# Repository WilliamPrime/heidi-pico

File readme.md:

HeidiBoard is my first attempt at a designing a devboard

Here are some features
- rp2040 microprocessor
- 16MiB of flash
- 1 wire temperature sensor
- pin compatible with pi pico
- fun Heidi artwork

here are some photos from design it:

here are some photos of the assembled working boards:
(to be added later)

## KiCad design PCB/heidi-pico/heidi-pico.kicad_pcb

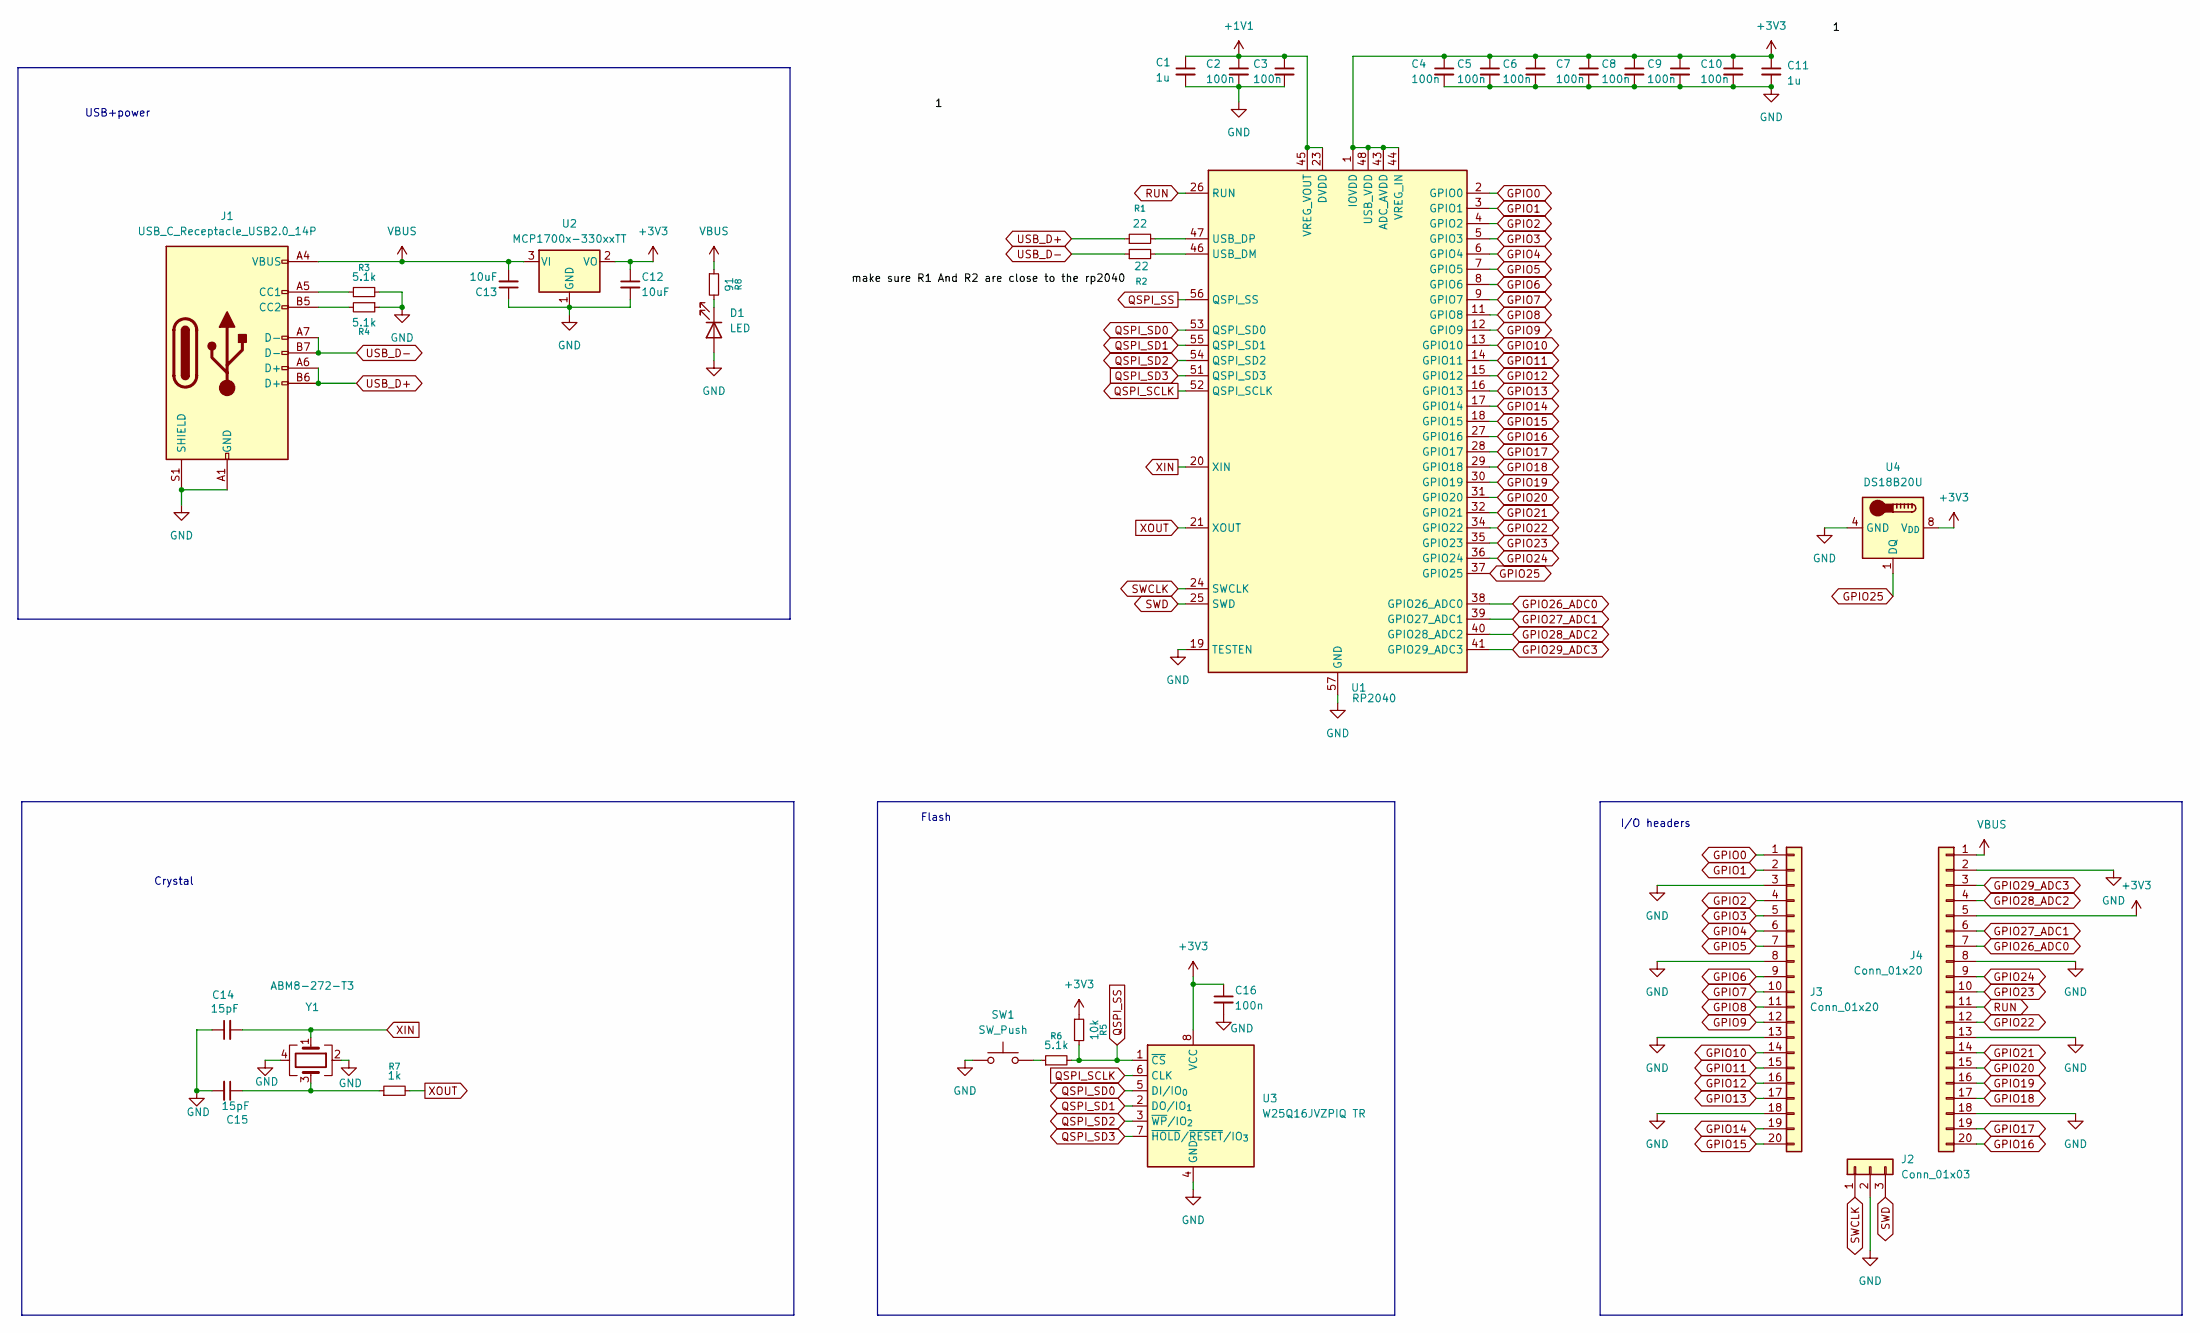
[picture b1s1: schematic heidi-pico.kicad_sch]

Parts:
C1, C11: 1u; C_0402_1005Metric
C2, C3, C4, C5, C6, C7, C8, C9, C10, C16: 100n; C_0402_1005Metric
C12, C13: 10uF; C_0603_1608Metric
C14, C15: 15pF; C_0402_1005Metric
D1: LED; LED_0603_1608Metric
J1: USB_C_Receptacle_USB2.0_14P; USB_C_Receptacle_HRO_TYPE-C-31-M-12
J2: Conn_01x03; PinHeader_1x03_P2.54mm_Vertical
J3, J4: Conn_01x20; PinHeader_1x20_P2.54mm_Vertical
R1, R2: 22; R_0402_1005Metric
R3, R4, R6: 5.1k; R_0402_1005Metric
R5: 10k; R_0402_1005Metric
R7: 1k; R_0402_1005Metric
R8: 91; R_0603_1608Metric
SW1: SW_Push; pushSwitch
U1: RP2040; QFN-56-1EP_7x7mm_P0.4mm_EP3.2x3.2mm
U2: MCP1700x-330xxTT; SOT-23
U3: W25Q16JVZPIQ TR; Winbond_USON-8-1EP_3x2mm_P0.5mm_EP0.2x1.6mm
U4: DS18B20U; MSOP-8_3x3mm_P0.65mm
Y1: ABM8-272-T3; Crystal_SMD_Abracon_ABM8G-4Pin_3.2x2.5mm

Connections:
+1V1: C1.1, C2.1, C3.1, U1.23 (DVDD), U1.45 (VREG_VOUT), U1.50 (DVDD)
+3V3: C4.1, C5.1, C6.1, C7.1, C8.1, C9.1, C10.1, C11.1, C12.1, C16.1, J4.5, R5.1, U1.1 (IOVDD), U1.10 (IOVDD), U1.22 (IOVDD), U1.33 (IOVDD), U1.42 (IOVDD), U1.43 (ADC_AVDD), U1.44 (VREG_IN), U1.48 (USB_VDD), U1.49 (IOVDD), U2.2 (VO), U3.8 (VCC), U4.8 (V_{DD})
GND: C1.2, C2.2, C3.2, C4.2, C5.2, C6.2, C7.2, C8.2, C9.2, C10.2, C11.2, C12.2, C13.1, C14.1, C15.2, C16.2, D1.2 (A), J1.A1 (GND), J1.A12 (GND), J1.B1 (GND), J1.B12 (GND), J1.S1 (SHIELD), J2.2, J3.3, J3.8, J3.13, J3.18, J4.2, J4.8, J4.13, J4.18, R3.2, R4.1, SW1.1, U1.19 (TESTEN), U1.57 (GND), U2.1 (GND), U3.4 (GND), U4.4 (GND), Y1.2, Y1.4
GPIO0: J3.1, U1.2 (GPIO0)
GPIO1: J3.2, U1.3 (GPIO1)
GPIO2: J3.4, U1.4 (GPIO2)
GPIO3: J3.5, U1.5 (GPIO3)
GPIO4: J3.6, U1.6 (GPIO4)
GPIO5: J3.7, U1.7 (GPIO5)
GPIO6: J3.9, U1.8 (GPIO6)
GPIO7: J3.10, U1.9 (GPIO7)
GPIO8: J3.11, U1.11 (GPIO8)
GPIO9: J3.12, U1.12 (GPIO9)
GPIO10: J3.14, U1.13 (GPIO10)
GPIO11: J3.15, U1.14 (GPIO11)
GPIO12: J3.16, U1.15 (GPIO12)
GPIO13: J3.17, U1.16 (GPIO13)
GPIO14: J3.19, U1.17 (GPIO14)
GPIO15: J3.20, U1.18 (GPIO15)
GPIO16: J4.20, U1.27 (GPIO16)
GPIO17: J4.19, U1.28 (GPIO17)
GPIO18: J4.17, U1.29 (GPIO18)
GPIO19: J4.16, U1.30 (GPIO19)
GPIO20: J4.15, U1.31 (GPIO20)
GPIO21: J4.14, U1.32 (GPIO21)
GPIO22: J4.12, U1.34 (GPIO22)
GPIO23: J4.10, U1.35 (GPIO23)
GPIO24: J4.9, U1.36 (GPIO24)
GPIO25: U1.37 (GPIO25), U4.1 (DQ)
GPIO26_ADC0: J4.7, U1.38 (GPIO26_ADC0)
GPIO27_ADC1: J4.6, U1.39 (GPIO27_ADC1)
GPIO28_ADC2: J4.4, U1.40 (GPIO28_ADC2)
GPIO29_ADC3: J4.3, U1.41 (GPIO29_ADC3)
unnamed: C15.1, R7.1, Y1.3
unnamed: D1.1 (K), R8.2
unnamed: J1.A5 (CC1), R3.1
unnamed: J1.B5 (CC2), R4.2
unnamed: R6.1, SW1.2
unnamed: R2.2, U1.46 (USB_DM)
unnamed: R1.2, U1.47 (USB_DP)
QSPI_SCLK: U1.52 (QSPI_SCLK), U3.6 (CLK)
QSPI_SD0: U1.53 (QSPI_SD0), U3.5 (DI/IO_{0})
QSPI_SD1: U1.55 (QSPI_SD1), U3.2 (DO/IO_{1})
QSPI_SD2: U1.54 (QSPI_SD2), U3.3 (~WP/IO_{2})
QSPI_SD3: U1.51 (QSPI_SD3), U3.7 (~HOLD/~RESET/IO_{3})
QSPI_SS: R5.2, R6.2, U1.56 (QSPI_SS), U3.1 (~CS)
RUN: J4.11, U1.26 (RUN)
SWCLK: J2.1, U1.24 (SWCLK)
SWD: J2.3, U1.25 (SWD)
USB_D+: J1.A6 (D+), J1.B6 (D+), R1.1
USB_D-: J1.A7 (D-), J1.B7 (D-), R2.1
VBUS: C13.2, J1.A4 (VBUS), J1.A9 (VBUS), J1.B4 (VBUS), J1.B9 (VBUS), J4.1, R8.1, U2.3 (VI)
XIN: C14.2, U1.20 (XIN), Y1.1
XOUT: R7.2, U1.21 (XOUT)

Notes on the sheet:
USB+power
I/O headers
Flash
Crystal

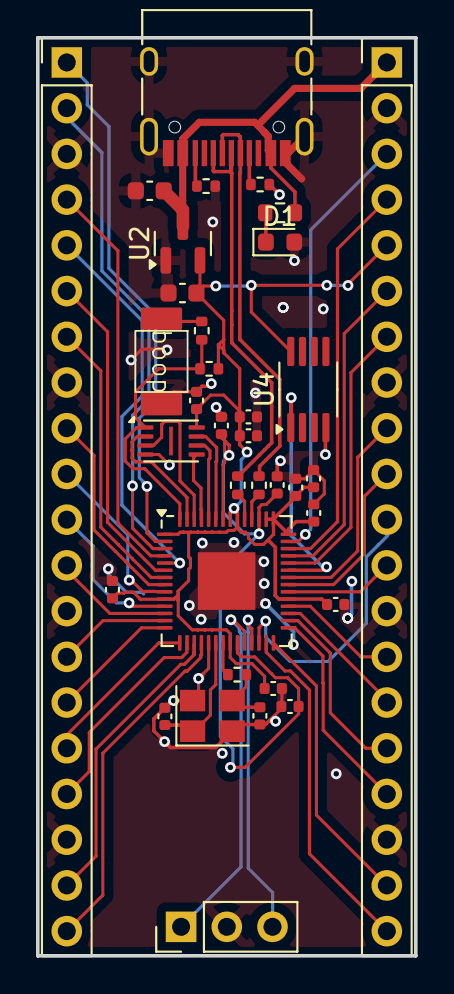
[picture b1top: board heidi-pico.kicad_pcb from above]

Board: 2 copper layers, 21.0 x 51.0 mm, 35 parts (0 on the bottom side), 54 nets.

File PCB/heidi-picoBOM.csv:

"Reference","Value","Footprint","Datasheet","Qty","DNP","Exclude from BOM","Exclude from Board"
"C1,C11","1u","Capacitor_SMD:C_0402_1005Metric","~","2","","",""
"C2,C3,C4,C5,C6,C7,C8,C9,C10,C16","100n","Capacitor_SMD:C_0402_1005Metric","~","10","","",""
"C12,C13","10uF","Capacitor_SMD:C_0603_1608Metric","~","2","","",""
"C14,C15","15pF","Capacitor_SMD:C_0402_1005Metric","~","2","","",""
"J1","USB_C_Receptacle_USB2.0_14P","Connector_USB:USB_C_Receptacle_HRO_TYPE-C-31-M-12","https://www.usb.org/sites/default/files/documents/usb_type-c.zip","1","","",""
"J2","Conn_01x03","Connector_PinHeader_2.54mm:PinHeader_1x03_P2.54mm_Vertical","~","1","","",""
"J3,J4","Conn_01x20","Connector_PinHeader_2.54mm:PinHeader_1x20_P2.54mm_Vertical","~","2","","",""
"R1,R2","22","Resistor_SMD:R_0402_1005Metric","~","2","","",""
"R3,R4,R6","5.1k","Resistor_SMD:R_0402_1005Metric","~","3","","",""
"R5","10k","Resistor_SMD:R_0402_1005Metric","~","1","","",""
"R7","1k","Resistor_SMD:R_0402_1005Metric","~","1","","",""
"SW1","SW_Push","Library:pushSwitch","~","1","","",""
"U1","RP2040","Package_DFN_QFN:QFN-56-1EP_7x7mm_P0.4mm_EP3.2x3.2mm","https://datasheets.raspberrypi.com/rp2040/rp2040-datasheet.pdf","1","","",""
"U2","MCP1700x-330xxTT","Package_TO_SOT_SMD:SOT-23","http://ww1.microchip.com/downloads/en/DeviceDoc/20001826D.pdf","1","","",""
"U3","W25Q16JVZPIQ TR","Package_SON:Winbond_USON-8-1EP_3x2mm_P0.5mm_EP0.2x1.6mm","https://www.winbond.com/resource-files/w25q128jv_dtr%20revc%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","1","","",""
"Y1","ABM8-272-T3","Crystal:Crystal_SMD_Abracon_ABM8G-4Pin_3.2x2.5mm","~","1","","",""

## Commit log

2026-01-11 asdf
2026-01-11 AHHHH ROUTING
2026-01-11 LCSC BOM
2026-01-17 minor changes
2026-01-20 added heidi art
2026-01-20 added readme plus BOM adjustments
2026-01-20 added drill files to most recent gerbers
